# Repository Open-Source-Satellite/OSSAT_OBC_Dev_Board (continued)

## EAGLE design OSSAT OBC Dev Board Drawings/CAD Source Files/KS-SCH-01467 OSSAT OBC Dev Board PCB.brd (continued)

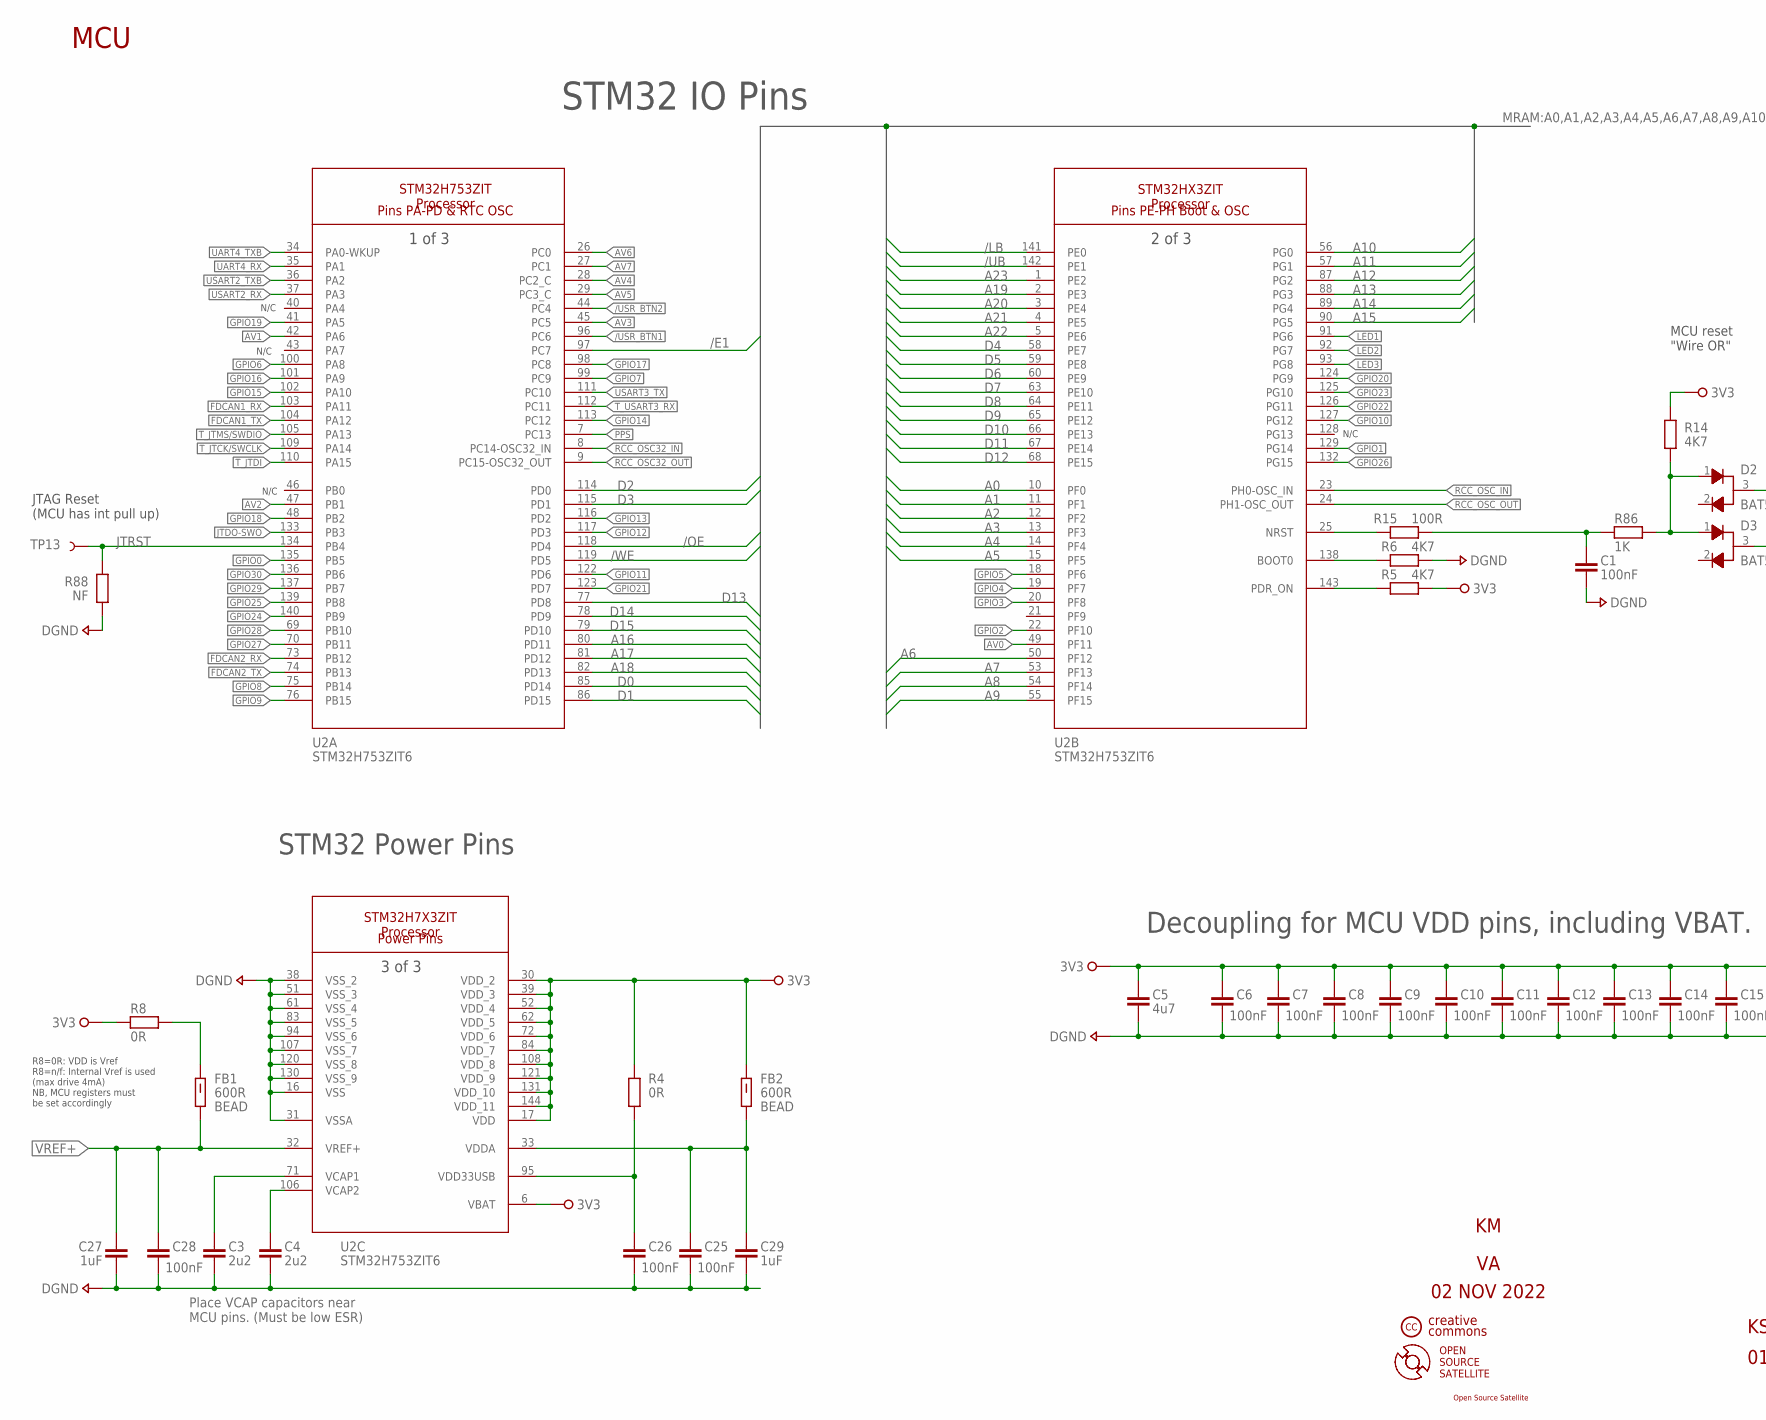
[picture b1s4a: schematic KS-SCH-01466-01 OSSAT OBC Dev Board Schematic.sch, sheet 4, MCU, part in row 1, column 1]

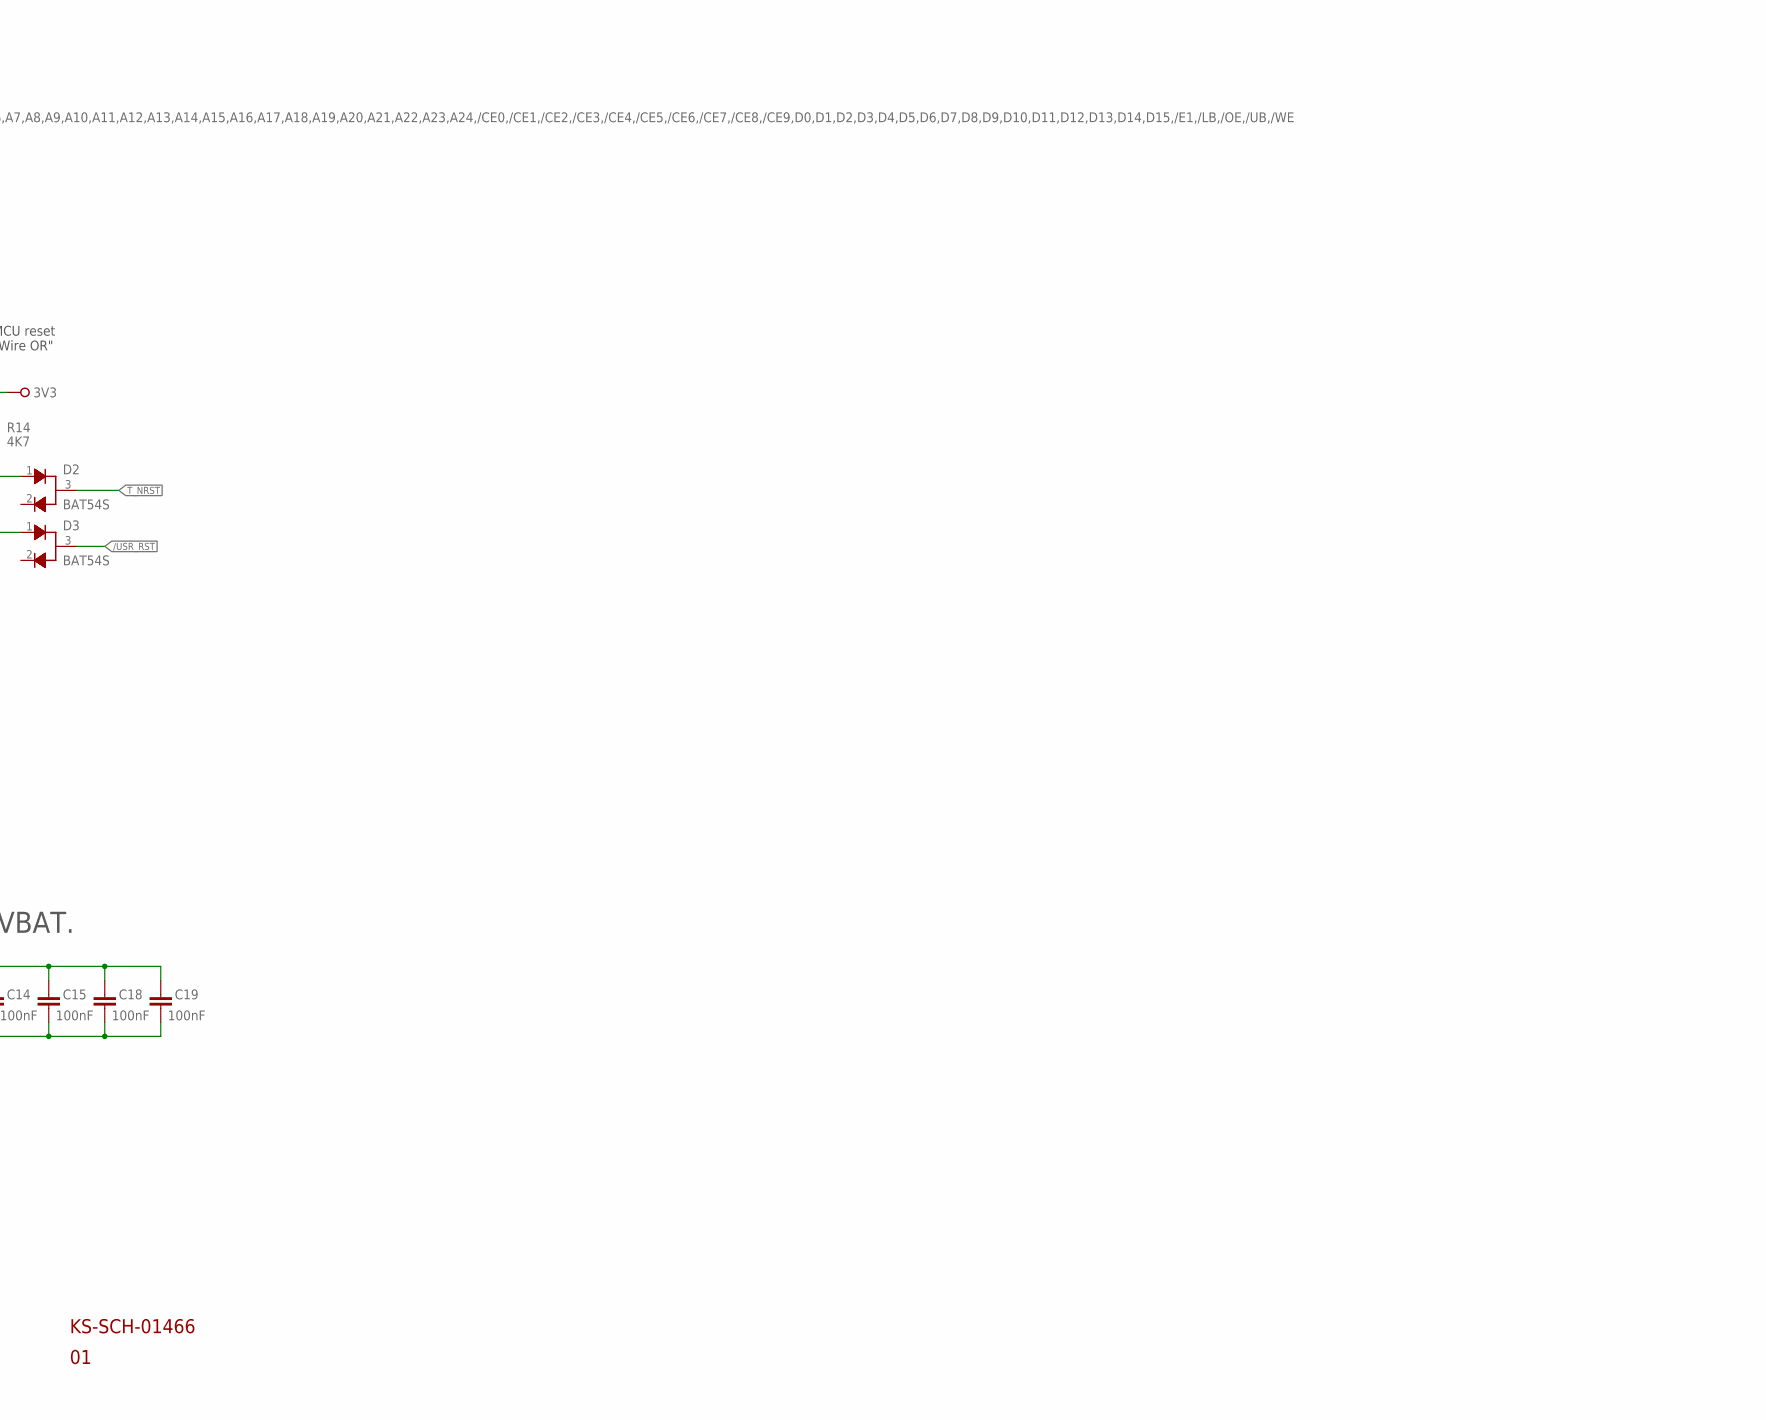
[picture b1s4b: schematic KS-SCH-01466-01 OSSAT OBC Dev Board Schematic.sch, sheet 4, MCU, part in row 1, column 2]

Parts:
C1, C6, C7, C8, C9, C10, C11, C12, C13, C14, C15, C18, C19, C25, C26, C28: 100nF; CAP_CHIP_0805
C3, C4: 2u2; CAP_CHIP_0805
C5: 4u7; CAP_CHIP_0805
C27, C29: 1uF; CAP_CHIP_0805
D2, D3: DIOC100A_BAT54S_DUAL_SCHOTTKY; SOT23
FB1, FB2: 600R; BEADC2012X105N
R4, R8: 0R; RES_CHIP_0805
R5, R6, R14: 4K7; RES_CHIP_0805
R15: 100R; RES_CHIP_0805
R86: 1K; RES_CHIP_0805
R88: NF; RES_CHIP_0805
TP13: NF; TP-40TH
U2: ICTP100A_STM32H753ZIT6_MCU_144PIN; IC_STM32H753ZIT6

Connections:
3V3: C5.1, C6.1, C7.1, C8.1, C9.1, C10.1, C11.1, C12.1, C13.1, C14.1, C15.1, C18.1, C19.1, FB2.2, R4.2, R5.1, R8.2, R14.1, U2.6 (VBAT), U2.17 (VDD), U2.30 (VDD_2), U2.39 (VDD_3), U2.52 (VDD_4), U2.62 (VDD_5), U2.72 (VDD_6), U2.84 (VDD_7), U2.108 (VDD_8), U2.121 (VDD_9), U2.131 (VDD_10), U2.144 (VDD_11); also elsewhere on the board
/E1: U2.97 (PC7); also elsewhere on the board
/LB: U2.141 (PE0); also elsewhere on the board
/OE: U2.118 (PD4); also elsewhere on the board
/UB: U2.142 (PE1); also elsewhere on the board
/USR_BTN1: U2.96 (PC6); also elsewhere on the board
/USR_BTN2: U2.44 (PC4); also elsewhere on the board
/USR_RST: D3.3; also elsewhere on the board
/WE: U2.119 (PD5); also elsewhere on the board
A0: U2.10 (PF0); also elsewhere on the board
A1: U2.11 (PF1); also elsewhere on the board
A2: U2.12 (PF2); also elsewhere on the board
A3: U2.13 (PF3); also elsewhere on the board
A4: U2.14 (PF4); also elsewhere on the board
A5: U2.15 (PF5); also elsewhere on the board
A6: U2.50 (PF12); also elsewhere on the board
A7: U2.53 (PF13); also elsewhere on the board
A8: U2.54 (PF14); also elsewhere on the board
A9: U2.55 (PF15); also elsewhere on the board
A10: U2.56 (PG0); also elsewhere on the board
A11: U2.57 (PG1); also elsewhere on the board
A12: U2.87 (PG2); also elsewhere on the board
A13: U2.88 (PG3); also elsewhere on the board
A14: U2.89 (PG4); also elsewhere on the board
A15: U2.90 (PG5); also elsewhere on the board
A16: U2.80 (PD11); also elsewhere on the board
A17: U2.81 (PD12); also elsewhere on the board
A18: U2.82 (PD13); also elsewhere on the board
A19: U2.2 (PE3); also elsewhere on the board
A20: U2.3 (PE4); also elsewhere on the board
A21: U2.4 (PE5); also elsewhere on the board
A22: U2.5 (PE6); also elsewhere on the board
A23: U2.1 (PE2); also elsewhere on the board
AV0: U2.49 (PF11); also elsewhere on the board
AV1: U2.42 (PA6); also elsewhere on the board
AV2: U2.47 (PB1); also elsewhere on the board
AV3: U2.45 (PC5); also elsewhere on the board
AV4: U2.28 (PC2_C); also elsewhere on the board
AV5: U2.29 (PC3_C); also elsewhere on the board
AV6: U2.26 (PC0); also elsewhere on the board
AV7: U2.27 (PC1); also elsewhere on the board
BOOT0: R6.2, U2.138 (BOOT0)
D0: U2.85 (PD14); also elsewhere on the board
D1: U2.86 (PD15); also elsewhere on the board
D2: U2.114 (PD0); also elsewhere on the board
D3: U2.115 (PD1); also elsewhere on the board
D4: U2.58 (PE7); also elsewhere on the board
D5: U2.59 (PE8); also elsewhere on the board
D6: U2.60 (PE9); also elsewhere on the board
D7: U2.63 (PE10); also elsewhere on the board
D8: U2.64 (PE11); also elsewhere on the board
D9: U2.65 (PE12); also elsewhere on the board
D10: U2.66 (PE13); also elsewhere on the board
D11: U2.67 (PE14); also elsewhere on the board
D12: U2.68 (PE15); also elsewhere on the board
D13: U2.77 (PD8); also elsewhere on the board
D14: U2.78 (PD9); also elsewhere on the board
D15: U2.79 (PD10); also elsewhere on the board
DGND: C1.2, C3.2, C4.2, C5.2, C6.2, C7.2, C8.2, C9.2, C10.2, C11.2, C12.2, C13.2, C14.2, C15.2, C18.2, C19.2, C25.2, C26.2, C27.2, C28.2, C29.2, R6.1, R88.1, U2.16 (VSS), U2.31 (VSSA), U2.38 (VSS_2), U2.51 (VSS_3), U2.61 (VSS_4), U2.83 (VSS_5), U2.94 (VSS_6), U2.107 (VSS_7), U2.120 (VSS_8), U2.130 (VSS_9); also elsewhere on the board
FDCAN1_RX: U2.103 (PA11); also elsewhere on the board
FDCAN1_TX: U2.104 (PA12); also elsewhere on the board
FDCAN2_RX: U2.73 (PB12); also elsewhere on the board
FDCAN2_TX: U2.74 (PB13); also elsewhere on the board
GPIO0: U2.135 (PB5); also elsewhere on the board
GPIO1: U2.129 (PG14); also elsewhere on the board
GPIO2: U2.22 (PF10); also elsewhere on the board
GPIO3: U2.20 (PF8); also elsewhere on the board
GPIO4: U2.19 (PF7); also elsewhere on the board
GPIO5: U2.18 (PF6); also elsewhere on the board
GPIO6: U2.100 (PA8); also elsewhere on the board
GPIO7: U2.99 (PC9); also elsewhere on the board
GPIO8: U2.75 (PB14); also elsewhere on the board
GPIO9: U2.76 (PB15); also elsewhere on the board
GPIO10: U2.127 (PG12); also elsewhere on the board
GPIO11: U2.122 (PD6); also elsewhere on the board
GPIO12: U2.117 (PD3); also elsewhere on the board
GPIO13: U2.116 (PD2); also elsewhere on the board
GPIO14: U2.113 (PC12); also elsewhere on the board
GPIO15: U2.102 (PA10); also elsewhere on the board
GPIO16: U2.101 (PA9); also elsewhere on the board
GPIO17: U2.98 (PC8); also elsewhere on the board
GPIO18: U2.48 (PB2); also elsewhere on the board
GPIO19: U2.41 (PA5); also elsewhere on the board
GPIO20: U2.124 (PG9); also elsewhere on the board
GPIO21: U2.123 (PD7); also elsewhere on the board
GPIO22: U2.126 (PG11); also elsewhere on the board
GPIO23: U2.125 (PG10); also elsewhere on the board
GPIO24: U2.140 (PB9); also elsewhere on the board
GPIO25: U2.139 (PB8); also elsewhere on the board
GPIO26: U2.132 (PG15); also elsewhere on the board
GPIO27: U2.70 (PB11); also elsewhere on the board
GPIO28: U2.69 (PB10); also elsewhere on the board
GPIO29: U2.137 (PB7); also elsewhere on the board
GPIO30: U2.136 (PB6); also elsewhere on the board
JTDO-SWO: U2.133 (PB3); also elsewhere on the board
JTRST: R88.2, TP13.P$1, U2.134 (PB4)
LED1: U2.91 (PG6); also elsewhere on the board
LED2: U2.92 (PG7); also elsewhere on the board
LED3: U2.93 (PG8); also elsewhere on the board
unnamed: C26.1, R4.1, U2.95 (VDD33USB)
unnamed: FB1.2, R8.1
unnamed: C25.1, C29.1, FB2.1, U2.33 (VDDA)
unnamed: C4.1, U2.106 (VCAP2)
unnamed: C3.1, U2.71 (VCAP1)
unnamed: R15.2, U2.25 (NRST)
unnamed: D2.1, D3.1, R14.2, R86.2
unnamed: R5.2, U2.143 (PDR_ON)
unnamed: C1.1, R15.1, R86.1
PPS: U2.7 (PC13); also elsewhere on the board
RCC_OSC32_IN: U2.8 (PC14-OSC32_IN); also elsewhere on the board
RCC_OSC32_OUT: U2.9 (PC15-OSC32_OUT); also elsewhere on the board
RCC_OSC_IN: U2.23 (PH0-OSC_IN); also elsewhere on the board
RCC_OSC_OUT: U2.24 (PH1-OSC_OUT); also elsewhere on the board
T_JTCK/SWCLK: U2.109 (PA14); also elsewhere on the board
T_JTDI: U2.110 (PA15); also elsewhere on the board
T_JTMS/SWDIO: U2.105 (PA13); also elsewhere on the board
T_NRST: D2.3; also elsewhere on the board
T_USART3_RX: U2.112 (PC11); also elsewhere on the board
UART4_RX: U2.35 (PA1); also elsewhere on the board
UART4_TXB: U2.34 (PA0-WKUP); also elsewhere on the board
USART2_RX: U2.37 (PA3); also elsewhere on the board
USART2_TXB: U2.36 (PA2); also elsewhere on the board
USART3_TX: U2.111 (PC10); also elsewhere on the board
VREF+: C27.1, C28.1, FB1.1, U2.32 (VREF+); also elsewhere on the board

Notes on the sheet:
Decoupling for MCU VDD pins, including VBAT.
STM32 IO Pins
Place VCAP capacitors near MCU pins. (Must be low ESR)
STM32 Power Pins
R8=0R: VDD is Vref R8=n/f: Internal Vref is used (max drive 4mA) NB, MCU registers must be set accordingly
N/C
MCU reset "Wire OR"
KS-SCH-01466
MCU
02 NOV 2022
JTAG Reset (MCU has int pull up)
OPEN SOURCE SATELLITE
creative commons
Open Source Satellite

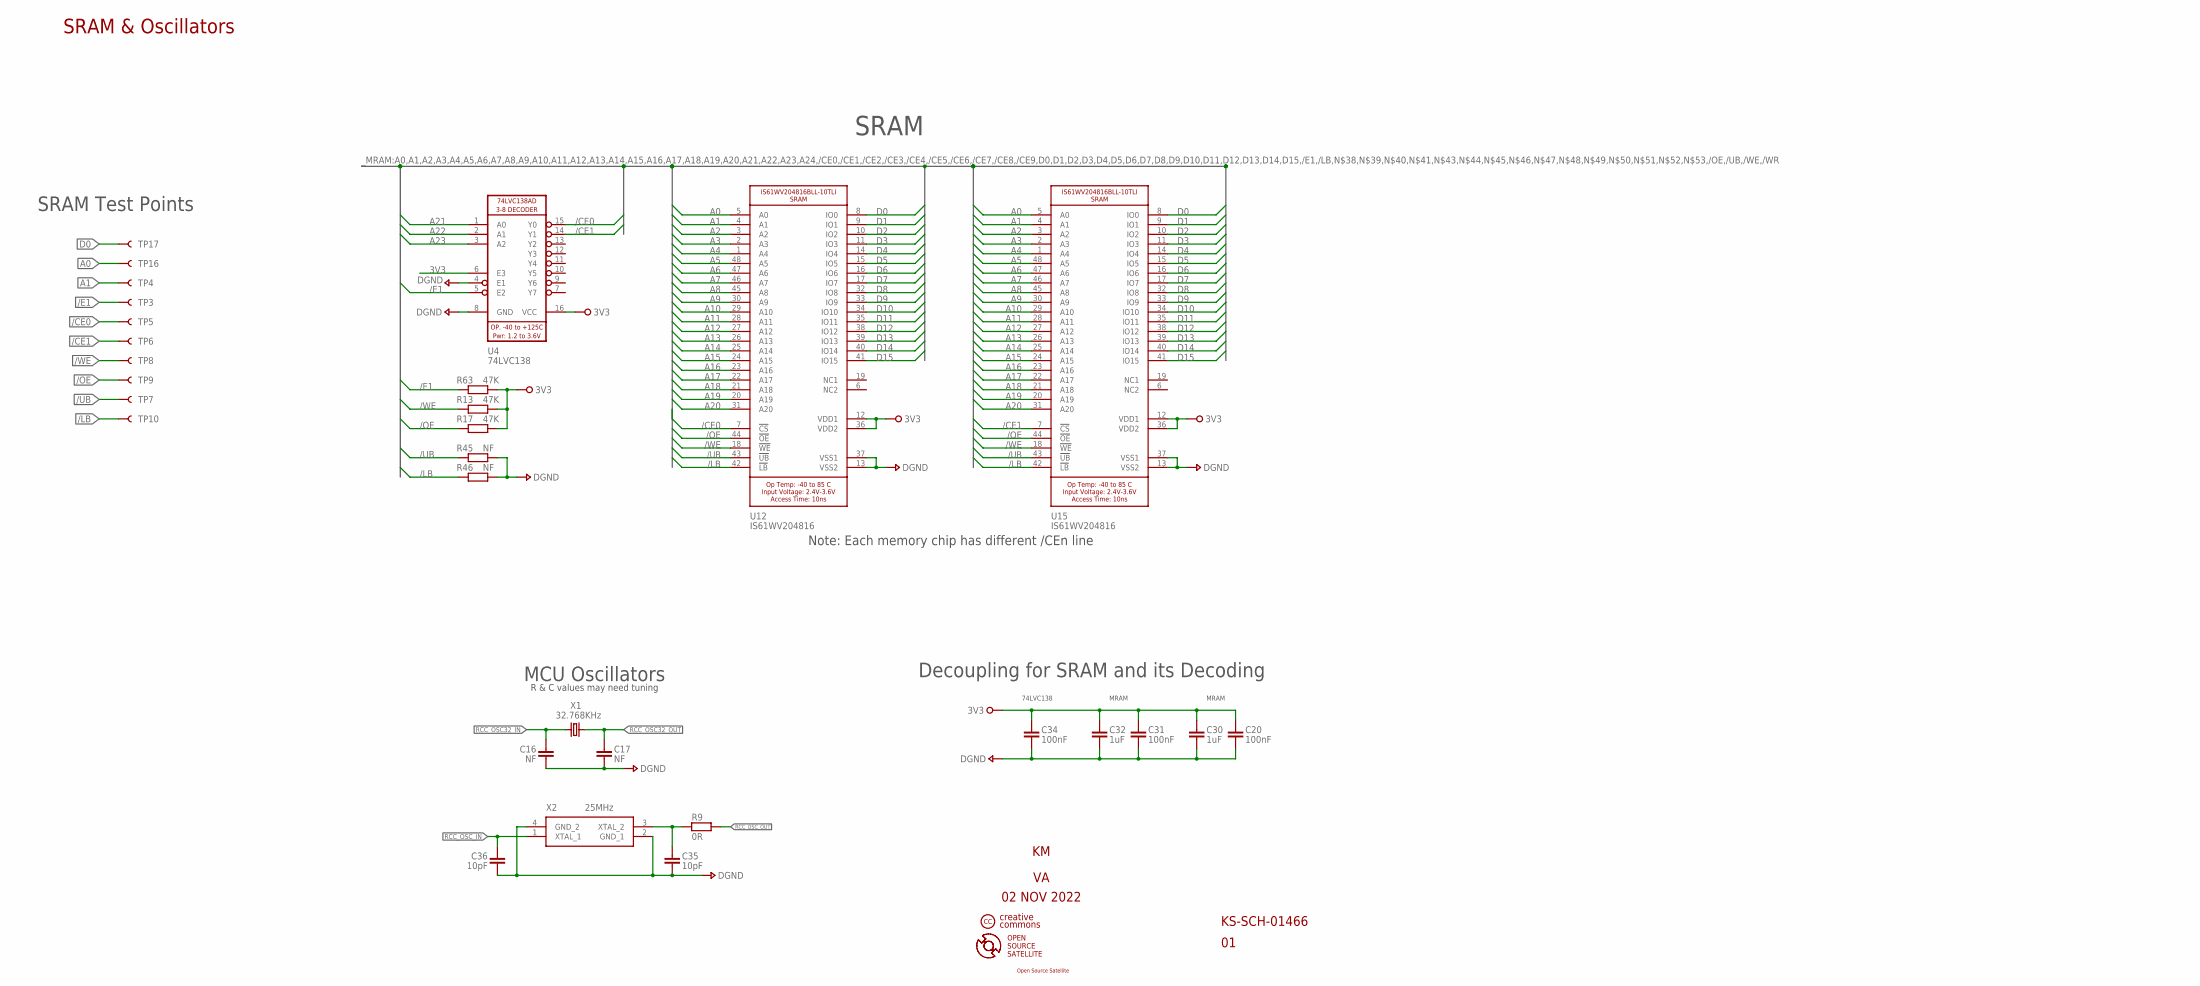
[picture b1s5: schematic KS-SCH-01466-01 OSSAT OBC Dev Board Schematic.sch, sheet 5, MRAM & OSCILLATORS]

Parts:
C16, C17: NF; CAP_CHIP_0805
C20, C31, C34: 100nF; CAP_CHIP_0805
C30, C32: 1uF; CAP_CHIP_0805
C35, C36: 10pF; CAP_CHIP_0805
R9: 0R; RES_CHIP_0805
R13, R17, R63: 47K; RES_CHIP_0805
R45, R46: NF; RES_CHIP_0805
TP3, TP4, TP5, TP6, TP7, TP8, TP9, TP10, TP16, TP17: NF; TP-40TH
U4: ICTL100A_74LVC138AD_3-8_DECODER; SOIC-16
U12, U15: ICTM101A_IS61WV204816BLL-10TLI_SRAM_4MBYTE; IS61WV204816BLL-10TLI
X1: OSCC100A_XTAL_32.768KHZ_12P5; XTAL_NX3215SA
X2: OSCC102A_XTAL_25MHZ_10PF; XTAL_NX2016SA

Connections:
3V3: C20.1, C30.1, C31.1, C32.1, C34.1, R13.2, R17.2, R63.2, U4.6 (E3), U4.16 (VCC), U12.12 (VDD1), U12.36 (VDD2), U15.12 (VDD1), U15.36 (VDD2); also elsewhere on the board
/CE0: TP5.P$1, U4.15 (Y0), U12.7 (!CS)
/CE1: TP6.P$1, U4.14 (Y1), U15.7 (!CS)
/E1: R63.1, TP3.P$1, U4.5 (E2); also elsewhere on the board
/LB: R46.1, TP10.P$1, U12.42 (!LB), U15.42 (!LB); also elsewhere on the board
/OE: R17.1, TP9.P$1, U12.44 (!OE), U15.44 (!OE); also elsewhere on the board
/UB: R45.1, TP7.P$1, U12.43 (!UB), U15.43 (!UB); also elsewhere on the board
/WE: R13.1, TP8.P$1, U12.18 (!WE), U15.18 (!WE); also elsewhere on the board
A0: TP16.P$1, U12.5 (A0), U15.5 (A0); also elsewhere on the board
A1: TP4.P$1, U12.4 (A1), U15.4 (A1); also elsewhere on the board
A2: U12.3 (A2), U15.3 (A2); also elsewhere on the board
A3: U12.2 (A3), U15.2 (A3); also elsewhere on the board
A4: U12.1 (A4), U15.1 (A4); also elsewhere on the board
A5: U12.48 (A5), U15.48 (A5); also elsewhere on the board
A6: U12.47 (A6), U15.47 (A6); also elsewhere on the board
A7: U12.46 (A7), U15.46 (A7); also elsewhere on the board
A8: U12.45 (A8), U15.45 (A8); also elsewhere on the board
A9: U12.30 (A9), U15.30 (A9); also elsewhere on the board
A10: U12.29 (A10), U15.29 (A10); also elsewhere on the board
A11: U12.28 (A11), U15.28 (A11); also elsewhere on the board
A12: U12.27 (A12), U15.27 (A12); also elsewhere on the board
A13: U12.26 (A13), U15.26 (A13); also elsewhere on the board
A14: U12.25 (A14), U15.25 (A14); also elsewhere on the board
A15: U12.24 (A15), U15.24 (A15); also elsewhere on the board
A16: U12.23 (A16), U15.23 (A16); also elsewhere on the board
A17: U12.22 (A17), U15.22 (A17); also elsewhere on the board
A18: U12.21 (A18), U15.21 (A18); also elsewhere on the board
A19: U12.20 (A19), U15.20 (A19); also elsewhere on the board
A20: U12.31 (A20), U15.31 (A20); also elsewhere on the board
A21: U4.1 (A0); also elsewhere on the board
A22: U4.2 (A1); also elsewhere on the board
A23: U4.3 (A2); also elsewhere on the board
D0: TP17.P$1, U12.8 (IO0), U15.8 (IO0); also elsewhere on the board
D1: U12.9 (IO1), U15.9 (IO1); also elsewhere on the board
D2: U12.10 (IO2), U15.10 (IO2); also elsewhere on the board
D3: U12.11 (IO3), U15.11 (IO3); also elsewhere on the board
D4: U12.14 (IO4), U15.14 (IO4); also elsewhere on the board
D5: U12.15 (IO5), U15.15 (IO5); also elsewhere on the board
D6: U12.16 (IO6), U15.16 (IO6); also elsewhere on the board
D7: U12.17 (IO7), U15.17 (IO7); also elsewhere on the board
D8: U12.32 (IO8), U15.32 (IO8); also elsewhere on the board
D9: U12.33 (IO9), U15.33 (IO9); also elsewhere on the board
D10: U12.34 (IO10), U15.34 (IO10); also elsewhere on the board
D11: U12.35 (IO11), U15.35 (IO11); also elsewhere on the board
D12: U12.38 (IO12), U15.38 (IO12); also elsewhere on the board
D13: U12.39 (IO13), U15.39 (IO13); also elsewhere on the board
D14: U12.40 (IO14), U15.40 (IO14); also elsewhere on the board
D15: U12.41 (IO15), U15.41 (IO15); also elsewhere on the board
DGND: C16.2, C17.2, C20.2, C30.2, C31.2, C32.2, C34.2, C35.2, C36.2, R45.2, R46.2, U4.4 (E1), U4.8 (GND), U12.13 (VSS2), U12.37 (VSS1), U15.13 (VSS2), U15.37 (VSS1), X2.2 (GND_1), X2.4 (GND_2); also elsewhere on the board
unnamed: C35.1, R9.2, X2.3 (XTAL_2)
RCC_OSC32_IN: C16.1, X1.2; also elsewhere on the board
RCC_OSC32_OUT: C17.1, X1.1; also elsewhere on the board
RCC_OSC_IN: C36.1, X2.1 (XTAL_1); also elsewhere on the board
RCC_OSC_OUT: R9.1; also elsewhere on the board

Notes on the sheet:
Note: Each memory chip has different /CEn line
SRAM
Decoupling for SRAM and its Decoding
74LVC138
MRAM
SRAM & Oscillators
KS-SCH-01466
SRAM Test Points
MCU Oscillators
R & C values may need tuning
02 NOV 2022
OPEN SOURCE SATELLITE
creative commons
Open Source Satellite

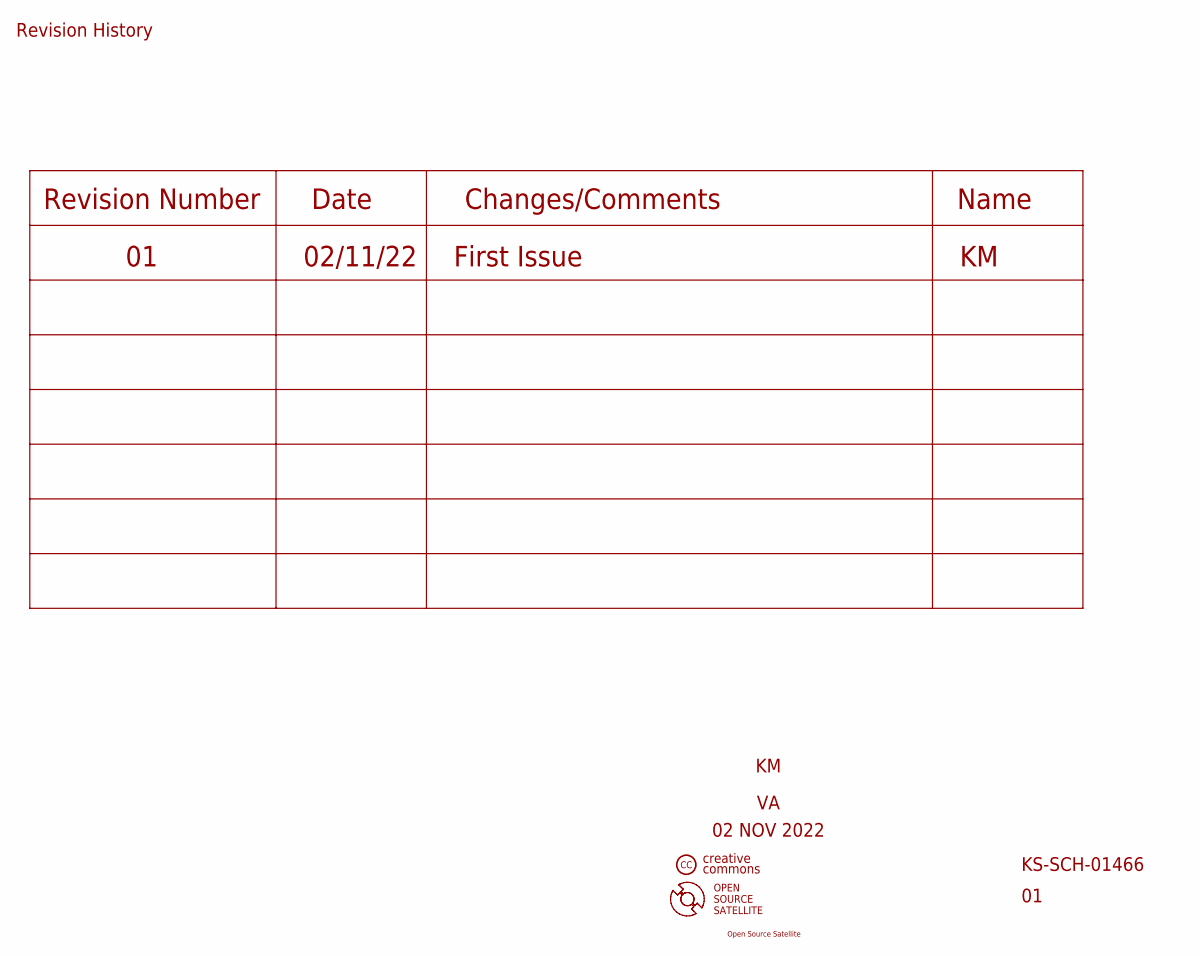
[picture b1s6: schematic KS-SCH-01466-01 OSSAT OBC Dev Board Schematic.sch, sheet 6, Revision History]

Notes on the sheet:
Revision History
KS-SCH-01466
Revision Number
Date
Changes/Comments
02/11/22
First Issue
Name
02 NOV 2022
OPEN SOURCE SATELLITE
creative commons
Open Source Satellite

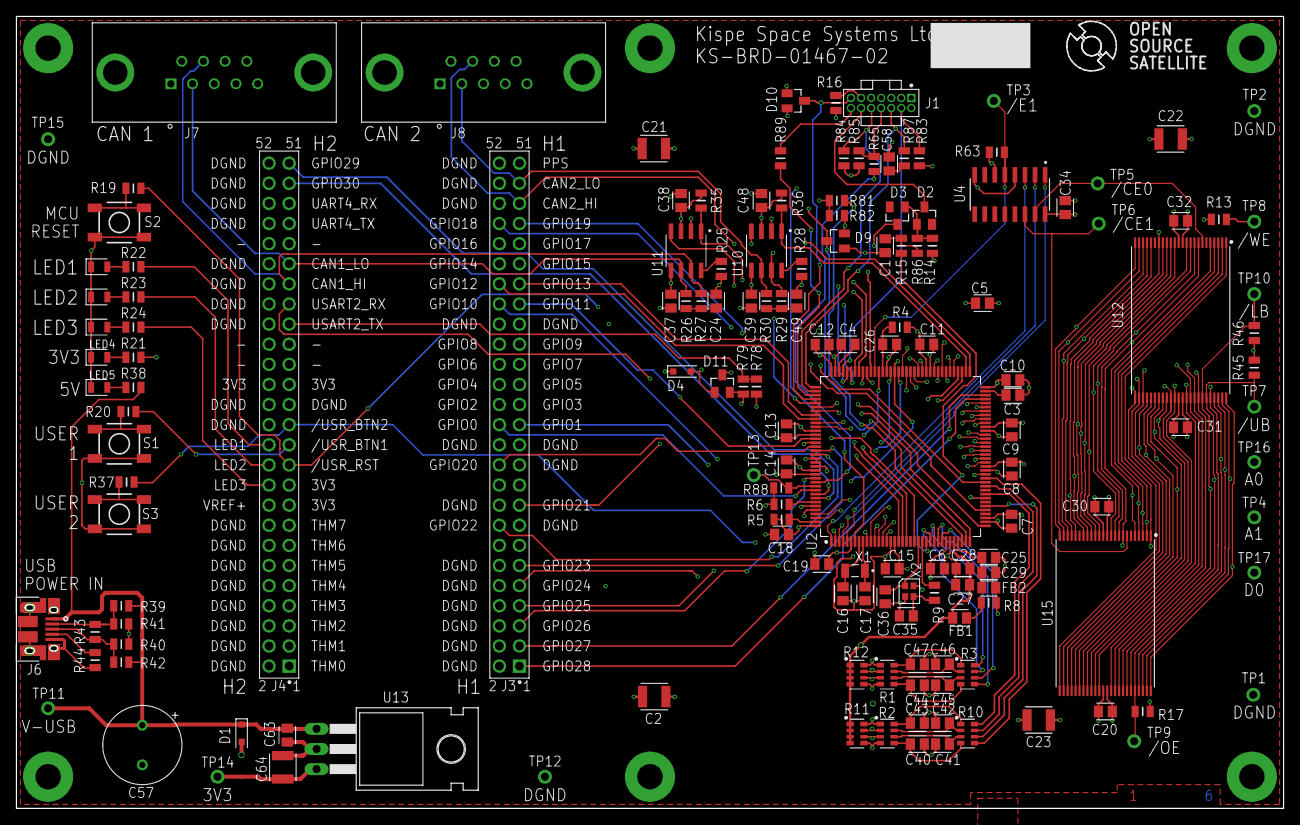
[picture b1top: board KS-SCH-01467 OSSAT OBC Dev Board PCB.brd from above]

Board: 6 copper layers, 160.0 x 100.0 mm, 160 parts (0 on the bottom side), 169 nets.

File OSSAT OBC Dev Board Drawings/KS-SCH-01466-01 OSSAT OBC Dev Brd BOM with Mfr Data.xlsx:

KS-SCH-01466-01 OSSAT OBC Dev Board Bill of Materials
To be used with shematic KS-SCH-01466-01 Schematic and KS-SCH-01466-02 PCB artw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
Item no | Qty | Refs | Description | Manufacturer | Manf Part number | Vendor | Stock No
1 | 1 | C58 | 100pF MLCC 0805 COG 50V 5% | Kemet | C0805C101J5GACTU | Farnell | 1414656
2 | 2 | C35, C36 | 10pF MLCC 0805 COG 50V 5% Q200 | Kemet | C0805C100J5GACAUTO | Farnell | 2070433
3 | 0 | C16, C17 | #N/A | #N/A | #N/A | #N/A | #N/A
4 | 24 | C1, C6, C7, C8, C9, C10, C11, C12, C13, C14, C15, C18, C19, C20, C25, C26, C28,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 | 100nF MLCC 0805 X7R 50V 10% | Kemet | C0805C104K5RACTU | Farnell | 1414664
5 | 2 | C24, C49 | 47nF MLCC 0805 X7R 50V 10% Q200 | Kemet | C0805C473K5RACAUTO | Farnell | 2070486
6 | 12 | C27, C29, C30, C32, C40, C41, C42, C43, C44, C45, C46, C47 | 1uF MLCC 0805 X7R 25V 10% | Kemet | C0805C105K3RECTU | Farnell | 2991344
7 | 1 | C5 | 4u7 MLCC 0805 X7R 16V 10% | Kemet | C0805C475K4RACTU | Farnell | 2118133
8 | 2 | C3, C4 | 2u2 MLCC 0805 X7R 16V 10% Q200 | Kemet | C0805C225K4RECAUTO | Farnell | 2991362
9 | 1 | C64 | 10uF MLCC 1210 X7R 25V 10% Q200 | Kemet | C1210C106K3RACAUTO | Farnell | 2070524
10 | 4 | C2, C21, C22, C23 | 47uF MLCC 1210 X7R 10V 10% | Murata | GRM32ER71A476KE15L | Farnell | 1797018
11 | 1 | C57 | 470uF ELECTROLYTIC 16V 20% PTH 10Dx12.5Hx5P Rubycon YXF | Rubycon | 16YXF470MEFC10X12.5 | Farnell | 1144616
12 | 2 | J3, J4 | 52F 2 Row Skt-Strip 2.54P Samtec ESQ-nnn-12-G-D | Samtec | ESQ-126-12-G-D | Farnell | 2856394
13 | 1 | J1 | 14M 2 Row Micro Header 1.27p Samtec FTSH-1nn-01-F-D-K | Samtec | FTSH-107-01-F-D-K | Mouser | 200-FTSH10701FDK
14 | 2 | J7, J8 | 9F D-Sub Vert Scw-Post Amphenol FCI DELTA-D | Amphenol FCI | LD09S24A4GV00LF | Farnell | 3367583
15 | 1 | J6 | Micro-USB 90deg Amphenol 10103594-0001LF | Amphenol | 10103594-0001LF | Farnell | 2293752
16 | 0 | TP1, TP2, TP3, TP4, TP5, TP6, TP7, TP8, TP9, TP10, TP11, TP12, TP13, TP14, TP15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 | #N/A | #N/A | #N/A | #N/A | #N/A
17 | 5 | D2, D3, D9, D10, D11 | BAT54S Dual Schottky SOT23 diodes in series | NXP | BAT54S,215 | Farnell | 1081194
18 | 1 | U4 | 74LVC138AD 3-8 decoder SOIC16 Max 125C | NXP | 74LVC138AD,118 | Farnell | 2463808
19 | 2 | U12, U15 | IS61WV204816BLL-10TLI SRAM 4MByte (2Mx16) 48pin-TSOP Max 85C | ISSI | IS61WV204816BLL-10TLI | Mouser | 870-WV204816BLL10TLI
20 | 1 | U2 | STM32H753ZIT6 MCU 144pin Max 85C | STM | STM32H753ZIT6 | Farnell | 2851002
21 | 1 | U13 | 3V3 LFnnABV LDO Regulator TO-220 Max 125C | STM | LF33ABV | Farnell | 1087184
22 | 2 | U10, U11 | MAX33054EASA+ CAN-Tranceiver SOIC8 Max 125C | Maxim | MAX33054EASA+ | Farnell | 2915380
23 | 2 | FB1, FB2 | 600R Bead 0805 600R at 100MHz WE-CBF-SMD | Wurth | 742792040 (WE-CBF-SMD) | Farnell | 1635735
24 | 0 | H1, H2, H3, H4, H5, H6 | #N/A | #N/A | #N/A | #N/A | #N/A
25 | 5 | LED1, LED2, LED3, LED4, LED5 | LED Yellow 0805 120deg 590nm 150mcd | Kingbright | APT2012SYCK | Mouser | 604-APT2012SYCK
26 | 1 | X1 | Xtal 32.768KHz 12p5 Max 125c Size 3.2x1.5x0.8 | NDK | NX3215SA-32.768K-STD-MUS-2 | Mouser | 344-NX3215SA32768K2
27 | 1 | X2 | Xtal 25MHz 10pF Max 125c Size 2.0x1.6x0.45 | Abracon | ABM11AIG-25.000MHZ-4Z-T3 | Farnell | 3819707
28 | 5 | R4, R8, R9, R25, R28 | 0R RES 0805 LINK 2A | NIC COMPONENTS | NRC10ZOTRF | Farnell | 3223535
29 | 5 | R15, R16, R19, R20, R37 | 100R RES 0805 0.125W 1% AEC-Q200 | Vishay | CRCW0805100RFKEA | Farnell | 1469862
30 | 3 | R83, R84, R85 | 10K RES 0805 0.125W 1% AEC-Q200 | Vishay | CRCW080510K0FHEAP | Farnell | 3546411
31 | 1 | R86 | 1K RES 0805 0.125W 1% AEC-Q200 | Vishay | CRCW08051K00FKEA | Mouser | 71-CRCW0805-1.0K-E3
32 | 1 | R43 | 200R RES 0805 0.125W 1% AEC-Q200 | Vishay | CRCW0805200RFKEA | Farnell | 1469895
33 | 1 | R38 | 2K RES 0805 0.125W 1% AEC-Q200 | Vishay | CRCW08052K00FKEA | Mouser | 71-CRCW0805-2.0K-E3
34 | 4 | R65, R78, R81, R89 | 33R RES 0805 0.125W 1% AEC-Q200 | Panasonic | ERJP06F33R0V | Farnell | 1750735
35 | 7 | R13, R17, R35, R36, R63, R79, R82 | 47K RES 0805 0.125W 1% AEC-Q200 | Vishay | CRCW080547K0FKEB | Farnell | 3546437
36 | 3 | R5, R6, R14 | 4K7 RES 0805 0.125W 1% AEC-Q200 | Vishay | CRCW08054K70FKEA | Farnell | 1469923
37 | 4 | R26, R27, R29, R30 | 60R4 RES 0805 0.125W 1% AEC-Q200 | Panasonic | ERJ6ENF60R4V | Farnell | 2303416
38 | 1 | R87 | 68R RES 0805 0.125W 1% AEC-Q200 | Vishay | RCS080568R0FKEA | Farnell | 3235183
39 | 4 | R21, R22, R23, R24 | 910R RES 0805 0.125W 1% AEC-Q200 | Vishay | CRCW0805910RFKEA | Mouser | 71-CRCW0805910RFKEA
40 | 0 | R39, R40, R41, R42, R44, R45, R46, R88 | #N/A | #N/A | #N/A | #N/A | #N/A
41 | 4 | R1, R2, R11, R12 | 10K RES 4-isolated 1206 1% Q200 | Bourns | CAY16A-1001F4LF | Farnell | 3754800
42 | 2 | R3, R10 | 1K RES 4-isolated 1206 1% Q200 | Bourns | CAY16A-1001F4LF | Farnell | 3754799
43 | 3 | S1, S2, S3 | 1PST SMD Momentary push-button 12V 50mA | Sparkfun | COM-08720 | Mouser | 474-COM-08720
44 | 1 | D4 | 3V3 TVS CDSOD323-Tnn 350W Unidirectional | Bourns | CDSOD323-T03 | Farnell | 2341910
45 | 1 | D1 | 5V0 TVS CDSOD323-Tnn 350W Unidirectional | Bourns | CDSOD323-T05 | Farnell | 2341914

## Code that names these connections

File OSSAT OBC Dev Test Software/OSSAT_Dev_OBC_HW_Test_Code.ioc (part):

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Mcu.Name=STM32H753ZITx
Mcu.Package=LQFP144
Mcu.UserName=STM32H753ZITx
PA0.Mode=Asynchronous
PA0.Signal=UART4_TX
PA1.Mode=Asynchronous
PA1.Signal=UART4_RX
PA10.Signal=GPIO_Input
PA11.Mode=FDCAN_Activate
PA11.Signal=FDCAN1_RX
PA12.Mode=FDCAN_Activate
PA12.Signal=FDCAN1_TX
PA13\ (JTMS/SWDIO).Mode=JTAG_5_pins
PA13\ (JTMS/SWDIO).Signal=DEBUG_JTMS-SWDIO
PA14\ (JTCK/SWCLK).Mode=JTAG_5_pins
PA14\ (JTCK/SWCLK).Signal=DEBUG_JTCK-SWCLK
PA15\ (JTDI).Mode=JTAG_5_pins
PA15\ (JTDI).Signal=DEBUG_JTDI
PA2.Mode=Asynchronous
PA2.Signal=USART2_TX
PA3.Mode=Asynchronous
PA3.Signal=USART2_RX
PA5.Signal=GPIO_Input
PA6.Signal=ADCx_INP3
PA8.Signal=GPIO_Output
PA9.Signal=GPIO_Input
PB1.Signal=ADCx_INP5
PB10.Mode=I2C
PB10.Signal=I2C2_SCL
PB11.Mode=I2C
PB11.Signal=I2C2_SDA
PB12.Mode=FDCAN_Activate
PB12.Signal=FDCAN2_RX
PB13.Mode=FDCAN_Activate
PB13.Signal=FDCAN2_TX
PB14.Signal=GPIO_Output
PB15.Signal=GPIO_Output
PB2.Signal=GPIO_Input
PB3\ (JTDO/TRACESWO).Mode=JTAG_5_pins
PB3\ (JTDO/TRACESWO).Signal=DEBUG_JTDO-SWO
PB4\ (NJTRST).Mode=JTAG_5_pins
PB4\ (NJTRST).Signal=DEBUG_JTRST
PB5.Signal=GPIO_Output
PB6.Mode=I2C
PB6.Signal=I2C1_SCL
PB7.Mode=I2C
PB7.Signal=I2C1_SDA
PB8.Mode=I2C
PB8.Signal=I2C4_SCL
PB9.Mode=I2C
PB9.Signal=I2C4_SDA
PC0.Signal=ADCx_INP10
PC1.Signal=ADCx_INP11
PC10.Mode=Asynchronous
PC10.Signal=USART3_TX
PC11.Mode=Asynchronous
PC11.Signal=USART3_RX
PC12.Signal=GPIO_Input
PC13.Mode=Calibration_1Hz
PC13.Signal=RTC_OUT_CALIB
PC14-OSC32_IN\ (OSC32_IN).Mode=LSE-External-Oscillator
PC14-OSC32_IN\ (OSC32_IN).Signal=RCC_OSC32_IN
PC15-OSC32_OUT\ (OSC32_OUT).Mode=LSE-External-Oscillator
PC15-OSC32_OUT\ (OSC32_OUT).Signal=RCC_OSC32_OUT
PC2_C.Mode=IN0-Single-Ended
PC2_C.Signal=ADC3_INP0
PC3_C.Mode=IN1-Single-Ended
PC3_C.Signal=ADC3_INP1
PC4.Signal=GPIO_Output
PC5.Signal=ADCx_INP8
PC6.Signal=GPIO_Input
PC7.Mode=NorPsramChipSelect1_1
PC7.Signal=FMC_NE1
PC8.Signal=GPIO_Input
PC9.Signal=GPIO_Output
PD0.Signal=FMC_D2_DA2
PD1.Signal=FMC_D3_DA3
PD10.Signal=FMC_D15_DA15
PD11.Signal=FMC_A16_CLE
PD12.Signal=FMC_A17_ALE
PD13.Signal=FMC_A18
PD14.Signal=FMC_D0_DA0
PD15.Signal=FMC_D1_DA1
PD2.Signal=GPIO_Input
PD3.Signal=GPIO_Input
PD4.Signal=FMC_NOE
PD5.Signal=FMC_NWE
PD6.Signal=GPIO_Input
PD7.Mode=TX_Only_Simplex_Unidirect_Master
PD7.Signal=SPI1_MOSI
PD8.Signal=FMC_D13_DA13
PD9.Signal=FMC_D14_DA14
PE0.Signal=FMC_NBL0
PE1.Signal=FMC_NBL1
PE10.Signal=FMC_D7_DA7
PE11.Signal=FMC_D8_DA8
PE12.Signal=FMC_D9_DA9
PE13.Signal=FMC_D10_DA10
PE14.Signal=FMC_D11_DA11
PE15.Signal=FMC_D12_DA12
PE2.Signal=FMC_A23
PE3.Signal=FMC_A19
PE4.Signal=FMC_A20
PE5.Signal=FMC_A21
PE6.Signal=FMC_A22
PE7.Signal=FMC_D4_DA4
PE8.Signal=FMC_D5_DA5
PE9.Signal=FMC_D6_DA6
PF0.Signal=FMC_A0
PF1.Signal=FMC_A1
PF10.Signal=GPIO_Output
PF11.Mode=IN2-Single-Ended
PF11.Signal=ADC1_INP2
PF12.Signal=FMC_A6
PF13.Signal=FMC_A7
PF14.Signal=FMC_A8
PF15.Signal=FMC_A9
PF2.Signal=FMC_A2
PF3.Signal=FMC_A3
PF4.Signal=FMC_A4
PF5.Signal=FMC_A5
PF6.Signal=GPIO_Output
PF7.Signal=GPIO_Output
PF8.Signal=GPIO_Output
PF9.Signal=GPIO_Input
PG0.Signal=FMC_A10
PG1.Signal=FMC_A11
PG10.Mode=NSS_Signal_Hard_Output
PG10.Signal=SPI1_NSS
PG11.Mode=TX_Only_Simplex_Unidirect_Master
PG11.Signal=SPI1_SCK
PG12.Signal=GPIO_Input
PG13.Signal=FMC_A24
PG14.Signal=GPIO_Output
PG15.Signal=GPXTI15
PG2.Signal=FMC_A12
PG3.Signal=FMC_A13
PG4.Signal=FMC_A14_BA0
PG5.Signal=FMC_A15_BA1
PG6.Signal=GPIO_Output
PG7.Signal=GPIO_Output
PG8.Signal=GPIO_Output
PG9.Signal=GPXTI9
PH0-OSC_IN\ (PH0).Mode=HSE-External-Oscillator
PH0-OSC_IN\ (PH0).Signal=RCC_OSC_IN
PH1-OSC_OUT\ (PH1).Mode=HSE-External-Oscillator
PH1-OSC_OUT\ (PH1).Signal=RCC_OSC_OUT
RCC.SYSCLKFreq_VALUE=64000000
board=custom

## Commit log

2023-01-05 Initial Checkin
2023-01-13 Kevin added my name
2023-01-13 Added Running the OSSAT Application section.
2023-01-13 corrected running the code on OBC section.
2023-01-13 adding the OBC code readme.
2023-01-13 added link to OBC code instructions.
2023-01-13 started readme.
2023-01-13 added build config
2023-01-13 Added build config screenshot.
2023-01-13 added ST Link info.
2023-01-16 added st link image
2023-01-16 trying jfif image
2023-01-16 Cropped image
2023-01-16 Screenshot_STM32
2023-01-16 added STM32 screenshot
2023-01-16 corrected reference to STM32 screenshot
2023-01-16 tera term initial checkin
2023-01-16 initial checkin CLI example.
2023-01-16 adding fdisk image
2023-01-16 adding powershell screenshot.
2023-01-16 Completed the readme.
2023-01-16 corrected image references.
2023-01-16 corrected markdown errors.
2023-01-16 removed redundant information.
2023-01-16 Adding license
2023-01-16 added license graphics
2023-01-16 Adding schematics
2023-01-16 adding CC license
2023-01-16 added license
2023-01-18 added sections.
2023-01-24 removing redundant data
2023-01-24 Added the test software
2023-01-24 commit for software release
2023-01-31 testing online editor
2023-01-31 added history image
2023-01-31 Added info from the manifesto
2023-01-31 altered image size
2023-01-31 adding newlines and correcting images
2023-01-31 fixing image woes
2023-01-31 removed review comments and changed following review.
2023-01-31 tried to center image
2023-01-31 adjusted image size
2023-01-31 corrected grammar
2023-01-31 Add files via upload
    Added Gerber manufacturing files in a zip file
2023-01-31 Add files via upload
    Added fusion 360 CAD source files, comprising Schematic, PCB and Library file. all in an old Eagle format, to ensure maximum conpatibility.
2023-02-01 Add files via upload
    Added BOM and PCB Layer stackup document
2023-02-01 Add files via upload
    Added first version of the Manual, for comment
2023-02-01 Add files via upload
    Added PCB assembly build document
2023-02-03 Update README.md
    Added the section: Intro to OBC Development Board
2023-02-03 Update README.md
    Edited formatting in the new Intro section to correct bullets
2023-02-03 Update README.md
    Additional formatting changes to final bullet list in Intro section
2023-02-03 Update README.md
    Corrected bad figure references in the Intro section
2023-02-03 Update README.md
    Added blank lines after figure captions in the Intro section
2023-02-03 Update README.md
    Edites of spacing of figure captions in Intro
2023-02-03 Update README.md
    Update to links for the new intro section and move manual section further down
2023-02-03 Update README.md
    Correcting links
2023-02-03 Update README.md
    Final edits to get links at the top working and remove test links form earlier edits
2023-02-03 Update README.md
    Re-ordered links at the top, to correspond with the main text
2023-02-07 trial of a link to a document.
2023-02-07 removed permalink
2023-02-07 removed test info and reordered the page.
2023-02-07 removed reference to Mercury GS
2023-02-08 Update README.md
    Interim save with partial update to document links
2023-02-08 Update README.md
    Added links for all but the verification document
2023-02-10 Add files via upload
    Added test doc for the board
2023-02-10 Update README.md
    Added link for test spec. (Test spec has now been added to Github)
2023-02-10 Add files via upload
    Corrected a typo
2023-02-10 Add files via upload
    Additional typo corrections
2023-02-13 Add files via upload
    Added 'n/a' in results boxes that do not need to be filled in.
2023-02-15 Update README.md
    Added a link to the manual
2023-02-15 Add files via upload
    Minor corrections to Schematic, to change MRAM references to SRAM, also removed RXDAT Ready Reference
2023-02-15 Add files via upload
    Minor update to verification procedure to remove reference to RD Data Rdy
2023-02-15 Add files via upload
    Minor corrections, including referencing the BOM and software correctly
2023-02-15 Add files via upload
    Various corrections, per review
2023-02-15 Delete KS-SCH-01466 V01 OSSAT OBC Dev Board Schematic.pdf
    File deleted, due to newer version with corrected name added
2023-02-15 Update README.md
    Updated the link to the PDF schematic, because name slightly changed
2023-02-15 corrected link
